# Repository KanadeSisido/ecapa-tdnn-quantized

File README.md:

# anam — The Living Anamnesis

高齢の方の日常の声を 24 時間記録するペンダントと、その記録から「次の診察で先生に伝えること」を整えるアプリ。医療・介護の現場で、ご本人が診察室で思い出せない・言いそびれる生活の様子（アナムネ＝問診・生活歴）を、医師やケアの担い手に届ける。

DevFest GDGoC Japan Hackathon 2026 の提出物。

```text
ペンダント（録音・保存）──BLE、約2時間ごと──▶ スマホアプリ（anam）──HTTPS──▶ pendant-api（Cloud Run）──▶ Gemini（Vertex AI）
  赤/黒の表示で録音中を示す            要約・相談・報告書・設定              記録・メモ・設定を保存       要約・診療サマリー・声の聞き取り
```

## できること

| 画面 | 内容 |
|---|---|
| ホーム | ペンダントの録音状態（本体の赤/黒の表示と同じ見た目）、同期・電源・保存量、今日のハイライト |
| 要約 | 本日の要約と、**声で相談**。大きな「押して話す」ボタンで話すと、音声をそのまま Gemini に渡して聞き取り・返答し、返答を読み上げる。相談で出た「診察で伝えるメモ」がたまる |
| 要約 → 医師向け報告書 | チャットではなく、メモ・記録の所見・本日の様子を 1 枚にまとめ、OS の共有シートで医師に渡す |
| ログ | 日ごとの文字起こし・要約・録音データの情報 |
| 診療 | 次回診療向けの「気になる点」。記録から Gemini で作り直せる |
| 設定 | 「クラウドに送信する」（初期値オフ）、「返答を読み上げる」、開発者向けの BLE 同期画面 |

起動時に、ロゴ（ペンダントに A を刻んだ形）が描かれる約 2 秒のアニメーションが出る。

## Google の技術

- **Gemini（Vertex AI 経由）**: 1 日の要約、診療向けサマリー（気になる点）、要約タブの相談、**声の相談（音声を直接渡して、聞き取りと返答を 1 回で得る）**。
- **Cloud Run**: pendant-api（FastAPI）をデプロイ。

## プライバシーの考え方

- **クラウド送信は初期値オフ。** オンにするときは確認ダイアログで同意を取る。オフの間、サーバーは Gemini に何も送らない（声の相談は 409 で断る）。
- 録音した相談の声は、送信後に端末から消す。
- ペンダントは録音中に前面が赤く、電源が切れると黒になる。周りの人にも録音していることが分かる。
- 診断はしない。画面と報告書に「自動要約であり診断ではない」と明記する。

## リポジトリの構成

| パス | 内容 |
|---|---|
| `pendant/mobile/` | アプリ（Android: Kotlin / Compose、iOS: SwiftUI、共通の同期ロジック: Kotlin Multiplatform）。[README](pendant/mobile/README.md)、画面の自動録画は [demo/](pendant/mobile/demo/README.md) |
| `pendant/fw/` | ペンダントのファームウェア（nRF54L15、Zephyr / NCS） |
| `pendant/hw/` | ペンダントの基板（KiCad）。Standard（CR2477）と Premium（Solar＋蓄電） |
| `pendant/docs/spec/` | ペンダントの仕様（電源・音声・保存・同期形式・RF・筐体など） |
| `pendant/brand/` | ロゴ（SVG）とアプリアイコン |
| `export/`、`app/`、`report/` | 話者照合（ECAPA-TDNN を INT8 化してスマホで動かす）の PoC。[下記](#話者照合-pocecapa-tdnn) |
| `server/` | pendant-api。API 仕様は `server/API.md`、デプロイは `server/deploy.sh` |

## アプリを動かす

1. サーバーの URL とトークンを置く（**Git に入れない**。トークンはチームから受け取る）。
   - Android: `pendant/mobile/local.properties` に `pendant.api.base=https://…` と `pendant.api.token=…`
   - iOS: `pendant/mobile/iosApp/Sources/Secrets.plist` に `ApiBase` と `ApiToken`（文字列）
   - 置かなければ、固定のデモデータと台本の返答で動く（サーバー無しで画面を見られる）。
2. ビルドする。
   ```bash
   cd pendant/mobile && source env.sh && ./gradlew :androidApp:assembleDebug   # APK: androidApp/build/outputs/apk/debug/
   ```
   iOS は `pendant/mobile/iosApp/iosApp.xcodeproj` を Xcode で開いて実行する（Kotlin の共通部分はビルド時に自動で作られる）。
3. 声の相談を使うときは、設定タブで「クラウドに送信する」をオンにする。

## デモの流れ（例）

1. 起動アニメーション → ホームで「録音中」（ペンダントの赤い表示と同じ）を見せる。
2. 要約タブで「押して話す」→「最近、膝が痛くて夜も眠れないの。先生に伝えておいてほしい」と話す → 返答が読み上げられ、メモに残る。
3. 「医師向け報告書にまとめる」→ 共有シートで送る。
4. 診療タブで「記録から作り直す（Gemini）」。
5. 終わったら、サーバーに残った会話とメモを消しておく（相談の文脈に混ざるため）。
   ```bash
   curl -X DELETE -H "Authorization: Bearer $TOKEN" $URL/assistant/messages
   ```

## 既知の制約

- サーバーの DB はデモ用（Cloud Run の `/tmp` に置いた SQLite）。再デプロイ・再起動で初期データに戻り、「クラウドに送信する」もオフに戻る。
- ペンダント本体（Premium）は試作段階で、電源・録音時間の実測は済んでいない。デモのアプリはサーバーのデモデータを表示する。
- 話者照合（ECAPA）は PoC で、モバイルアプリにはまだ組み込んでいない。
- Android の声の相談は、実機での録音から返答までの通しを確認していない（iOS Simulator では確認済み）。

---

## 話者照合 PoC（ECAPA-TDNN）

SpeechBrain `spkrec-ecapa-voxceleb` を ONNX + INT8 に変換し、Flutter（ONNX Runtime）で
「登録音声と今の発話が同一人物か」をオンデバイスで判定する。

### 構成

```
export/                 Python: 変換・量子化・評価
  export_onnx.py        生波形→埋め込み を1本の ONNX に（Fbank もグラフに同梱）
  prepare_data.py       評価用 LibriSpeech test-clean 抽出（40話者×12発話）
  quantize_eval.py      INT8 量子化（dynamic / static QDQ）＋ EER・速度比較 → app/assets にコピー
  check_ort115.py       Flutter 同梱の ORT 1.15.1 でロードできるか確認
app/                    Flutter アプリ（Android / iOS）
  lib/speaker_verifier.dart  ORT 推論・コサイン類似度・PCM変換・簡易VAD
  lib/main.dart              登録（3回）→ 照合 UI、閾値スライダー
```

### 再生成手順

```bash
cd export
uv sync                       # torch 等で約1.3GB
uv run python export_onnx.py  # models/ecapa_fp32.onnx
uv run python prepare_data.py
uv run python quantize_eval.py
## 任意: 古い ORT での互換確認（新しい glibc では GLIBC_TUNABLES が必要）
GLIBC_TUNABLES=glibc.rtld.execstack=2 uv run --no-project --python 3.11 \
  --with onnxruntime==1.15.1 --with "numpy<2" --with soundfile python check_ort115.py

cd ../app
flutter run   # 実機推奨（マイクを使うため）
```

### 結果（LibriSpeech test-clean、キャリブ話者を除く 31話者433発話 / 先頭4秒、x86 CPU 1スレッド）

| model | size | EER | EER閾値 | fp32との cos | 3秒音声の推論 |
|---|---|---|---|---|---|
| fp32 | 84.1 MB | 0.80 % | 0.327 | 1.000 | 226 ms |
| int8 dynamic | 22.0 MB | 0.78 % | 0.334 | 0.995 | 320 ms |
| **int8 static (QDQ)** ← 採用 | 25.8 MB | 0.78 % | 0.329 | 0.996 | **46 ms** |

※ 評価セットは小さく、条件の良い英語の読み上げ音声。実運用では日本語・実機マイク・雑音環境での再評価と閾値調整が必須。

### ハマりどころ（対処済み）

- **ASP のマスク長計算まで量子化すると可変長入力で壊れる** → 量子化対象を Conv/MatMul に限定
- **ORT 1.31 の QDQ 融合が最終 fc Conv でクラッシュ** → そのノードだけ FP32 のまま
- **量子化ツールが付ける未使用 opset（ai.onnx.ml v5 等）で ORT 1.15 がロード拒否** → 未使用の opset 宣言を削除
- 前処理（DFT conv / log-mel）は FP32 のまま（量子化すると精度が落ちるため）

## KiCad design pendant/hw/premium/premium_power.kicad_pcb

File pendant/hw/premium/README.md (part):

# Premium power: circuit draft for review only

**Do not connect a real primary cell or hybrid capacitor (including Vina VPC and Eaton HSH/HSL).** Bare-board [prototype fabrication files](fab/README.md) are available for evaluation, but this electrical draft is not qualified for real-cell operation. D1 = BAT41ZFILM and R6 = 1.2 kΩ 1% are **emulator-only screening candidates**, not qualified primary-cell protection. They are placed before every primary branch including BQ25505 VBAT_PRI, consistent with Panasonic's [primary-cell caution](https://industrial.panasonic.com/cdbs/www-data/pdf/AAA4000/AAA4000COL15.pdf). Check the exact cell's reverse charge and fault requirements, leakage, forward drop, surge and operating temperatures. LM66100 U4 does not replace that requirement. Confirm diode-short, reversed-cell and failure current limits.

The demo evaluation target is a single CR2032 backup cell for 24 hours. SMD components are on the front; provisional through-hole footprints put the CH005-2032LF holder and horizontal Vina capacitor side by side on the back, with their leads hand-soldered from the front. Bare test pads are also on the back and have been moved outside their approximate courtyards. Pad-in-via is accepted for home assembly, subject to solder wicking and insulation checks. The user reported physical checks of the holder and capacitor on 2026-11-06; individual measured values were not supplied. Enclosure interference, test-pad access and backup runtime remain unverified. The selected first evaluation panel is the uxcell round 36 mm candidate, whose actual Voc, MPP and thickness have not been measured. R3/R4/R5 now use 787 kΩ / 6.34 MΩ / 4.87 MΩ, 0.1%, for nominal falling/rising VBAT_OK of 2.785 / 2.981 V. This gives the Vina 30 F's 2.5 V operating floor more static margin than the prior draft; it does not protect against self-discharge in storage or establish dynamic margin. It also reduces available energy before switching. See the design calculation and bench conditions. The new divider remains an evaluation candidate, not evidence that the schematic is safe or complete.

The candidate source paths are `VSTOR → U3 LM66100 → Q1 common-source back-to-back → VOR`, and `cell emulator → D1 → R6 → COIN → U4 LM66100 → Q2 common-source back-to-back → VOR`. BQ VBAT_PRI is sensed at COIN, downstream of D1/R6. Both LM66100 comparators use CE=their own VOUT. A LM66100 permits transient and small reverse current and has temperature-dependent leakage. Neither the primary cell nor the secondary energy path has been proven safe, and all startup and switching states require bench measurement with emulators.

For C1/C3/C5/C6, 10 µF 16 V and 0805 are provisional, with [Yageo CC0805KRX5R7BB106](https://www.yageogroup.com/download/specsheet/CC0805KRX5R7BB106) as a candidate. Actual capacitors still need bias, tolerance, temperature and leakage checks; the BQ solar input and VSTOR each require ≥4.7 µF **effective**. C8 is an intentionally unselected primary-side reservoir after D1/R6; its 1210 footprint is a placement placeholder, not a capacitance selection. Its value, actual size, leakage and failure effects are not validated, and VOR holdup is also not sized. J1 has provisional solder-wire pads; J2 and J3 use evaluation footprints for the horizontal Vina capacitor and CH005-2032LF holder. On 2026-11-06 the user reported checking both physical parts, including terminal polarity, hole locations and lead bends; measured values were not recorded. L1's Coilcraft land pattern has been compared with [LPS4018](https://www.coilcraft.com/getmedia/31b05c96-4c4c-4498-8dbb-fe092de76bad/lps4018.pdf). L2 now uses a local footprint with nominal pad dimensions following the [DFE201612E recommended pattern](https://elektronik.ropla.eu/pdf/stock/mur/dfe201612eseries.pdf); assembly remains untested.

The local `premium.pretty` library contains provisional TI RGR0020A and CSD75208W1015 footprints. BQ's external copper pads and four exposed-pad paste openings follow the example dimensions in the [BQ25505 package drawing](https://www.ti.com/lit/ds/symlink/bq25505.pdf). The CSD top-view copper pattern follows [TI §7.2](https://www.ti.com/lit/gpn/csd75208w1015), but **its F.Paste is intentionally absent**: a stencil generated as-is will have no paste openings for Q1/Q2. Determine the stencil and solder-mask design with the assembler before fabrication. Both footprints still need manufacturing and assembly verification, including BQ thermal vias if used. NAND's 8 × 6 mm / 1.27 mm pitch and nominal 3.4 × 4.3 mm exposed pad match the [F35UQA512M package drawing](https://cdn.icstop.com/upload/pdfs/e7/de/e7decc6bb7e9f2384da286e27083f166.pdf), but its EP electrical treatment and stencil need confirmation.

BQ NC pins 6/16/17 and exposed pad connect to GND. U2 is the provisional TPS62842DGRR, selected from the TPS62840 family because the smaller TPS62840DLCR was unavailable from the checked distributor. Its DGR package is larger and **not pin-compatible** with DLC: VSET pin 4 = GND selects 1.8 V, pin 7 is NC, and exposed pad 9 = GND. The unused DLC STOP function has no DGR pin. The provisional KiCad generic footprint has 0.50 mm outer pad width versus 0.30 mm in TI's land example; EP mask and paste also differ. Confirm the selected footprint and stencil with the assembler, along with output accuracy, effective capacitance and transients before PCB release. [TI device comparison, Table 1 and package example](https://www.ti.com/lit/ds/symlink/tps62840.pdf).

U5 is the SN74LVC1G17DBVR evaluation buffer: DBV pin 1 NC, 2 A from VBAT_OK_RAW, 3 GND, 4 Y to VBAT_OK_1V8, 5 VCC=1V8, with C7 100 nF. Its output goes to U103 B2/P0.03; TP12 is raw VBAT_OK and must not connect to a 1.8 V GPIO. Verify input thresholds, leakage, rail-off back-power, the input state when VSTOR is absent but the primary source powers 1V8, and the energy budget before adoption. [TI pinout and Ioff](https://www.ti.com/lit/ds/symlink/sn74lvc1g17.pdf). No HSL/COIN voltage dividers are connected: a divider alone must not energize a powered-off MCU through its ADC. P1.05/AIN1 is reserved but unconnected.

## Demo shared core and measurements

The sheet includes the BC15M U103, F35UQA512M U105, T5848 U108, microphone switch/buffer, button and SWD pogo from the Standard definitions. The optional external RTC and terminal-indicator circuits are omitted for this demo; no claim is made that the omitted product functions work. SW101 is a **bridged solder jumper**, not an operable privacy latch. Select and validate the actual physical control and check mic SD/WAKE back-power and isolation.

For the demo, NAND shares 1V8 through 0 Ω R106 and is **not independently power-gated**. This avoids the previous steady state in which a powered MCU could drive an unpowered NAND's pins, and removes the load switch and EN pulldown. It does not prove ramp or signal-transition behavior. The NAND datasheet gives 10 µA typ / 50 µA max standby under its stated conditions: account for that separately, rather than reusing a gated-NAND energy estimate. NAND remains powered on the coin source; firmware must separately prevent unqualified writes, erases, BLE and OTA. Before opening R106 for current measurement, de-energize and connect the meter without leaving a powered MCU driving an unpowered NAND; verify the meter's burden and all transitions.

R7 is the 1V8 main measurement link, R8 is the CAP measurement link; TP1–TP12 expose SOLAR, BQ-side HSL, VSTOR, protected COIN, VOR, 1V8_BUCK, SEC_GATE, PRI_GATE, CAP_EXT, MIC_EN, VBAT_OK_1V8 and VBAT_OK_RAW respectively. TP104/105/106/107 expose 1V8, NAND_1V8, MIC_1V8 and GND; the core also retains UART, marker and MIC_1V8_PRE points. J1 is a provisional solar interface; J2 and J3 use provisional physical capacitor and holder footprints whose mechanics and polarity require verification. The test fixture must not bypass the primary protection or become a USB supply path in the demo.

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
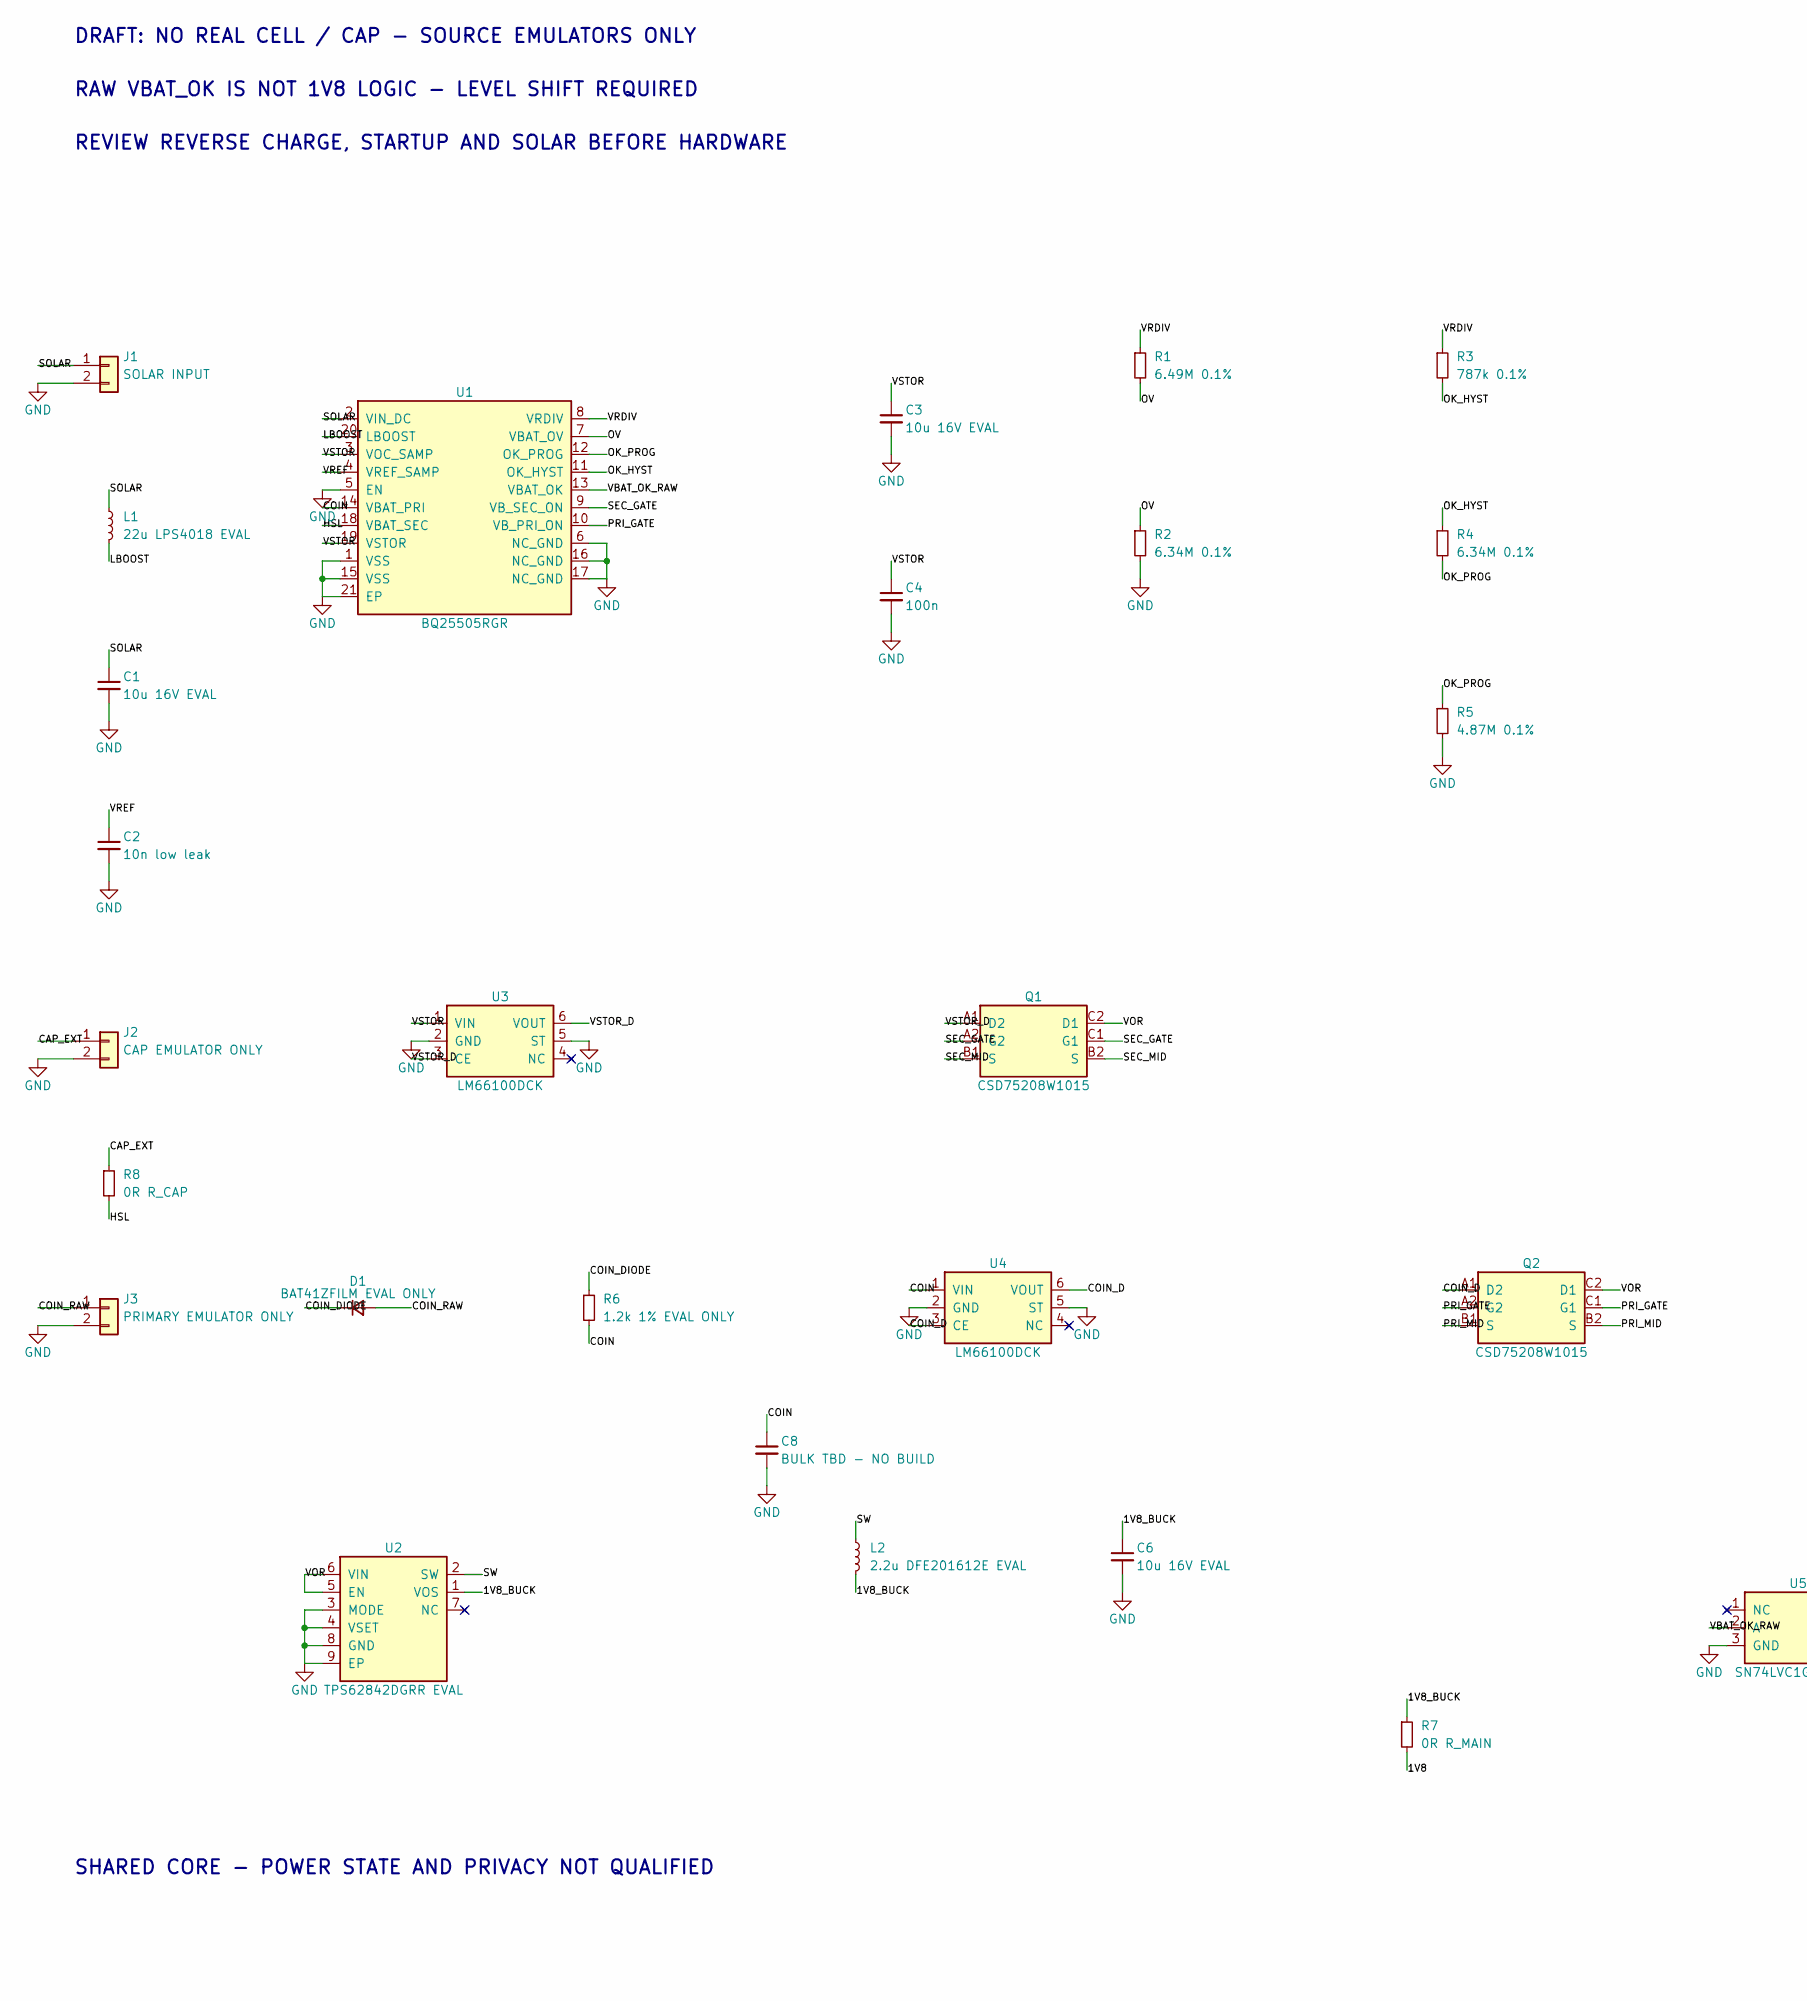
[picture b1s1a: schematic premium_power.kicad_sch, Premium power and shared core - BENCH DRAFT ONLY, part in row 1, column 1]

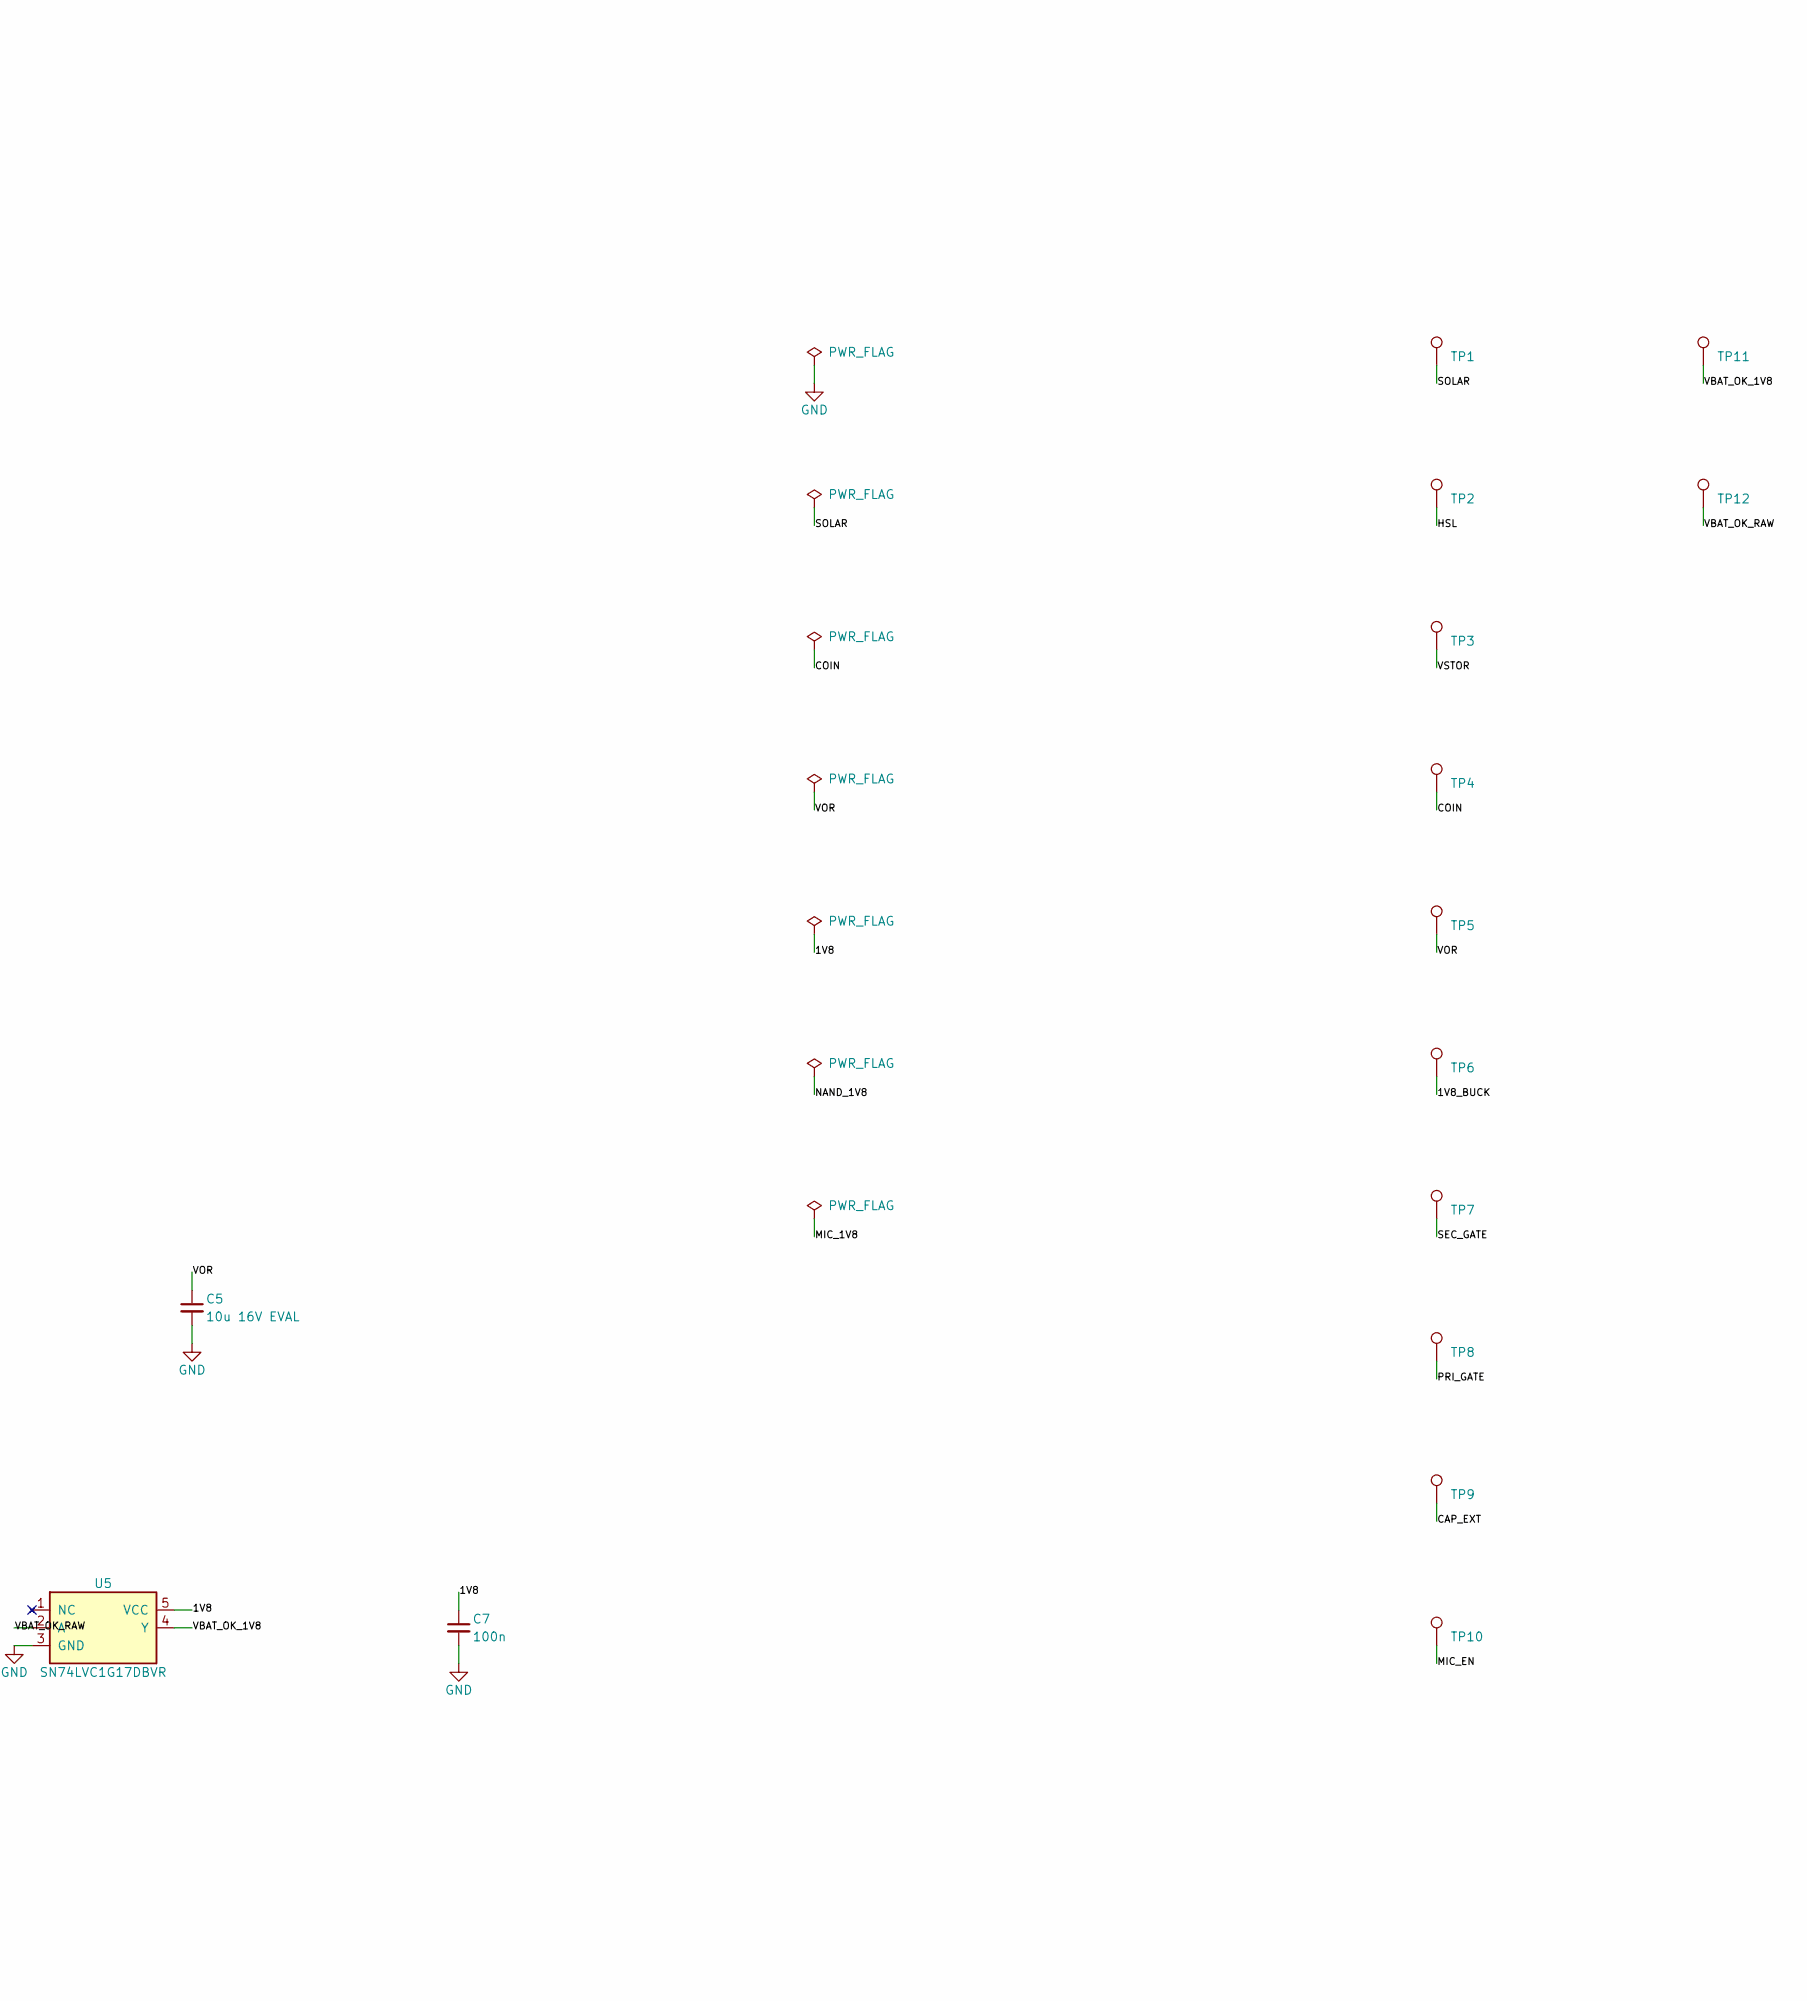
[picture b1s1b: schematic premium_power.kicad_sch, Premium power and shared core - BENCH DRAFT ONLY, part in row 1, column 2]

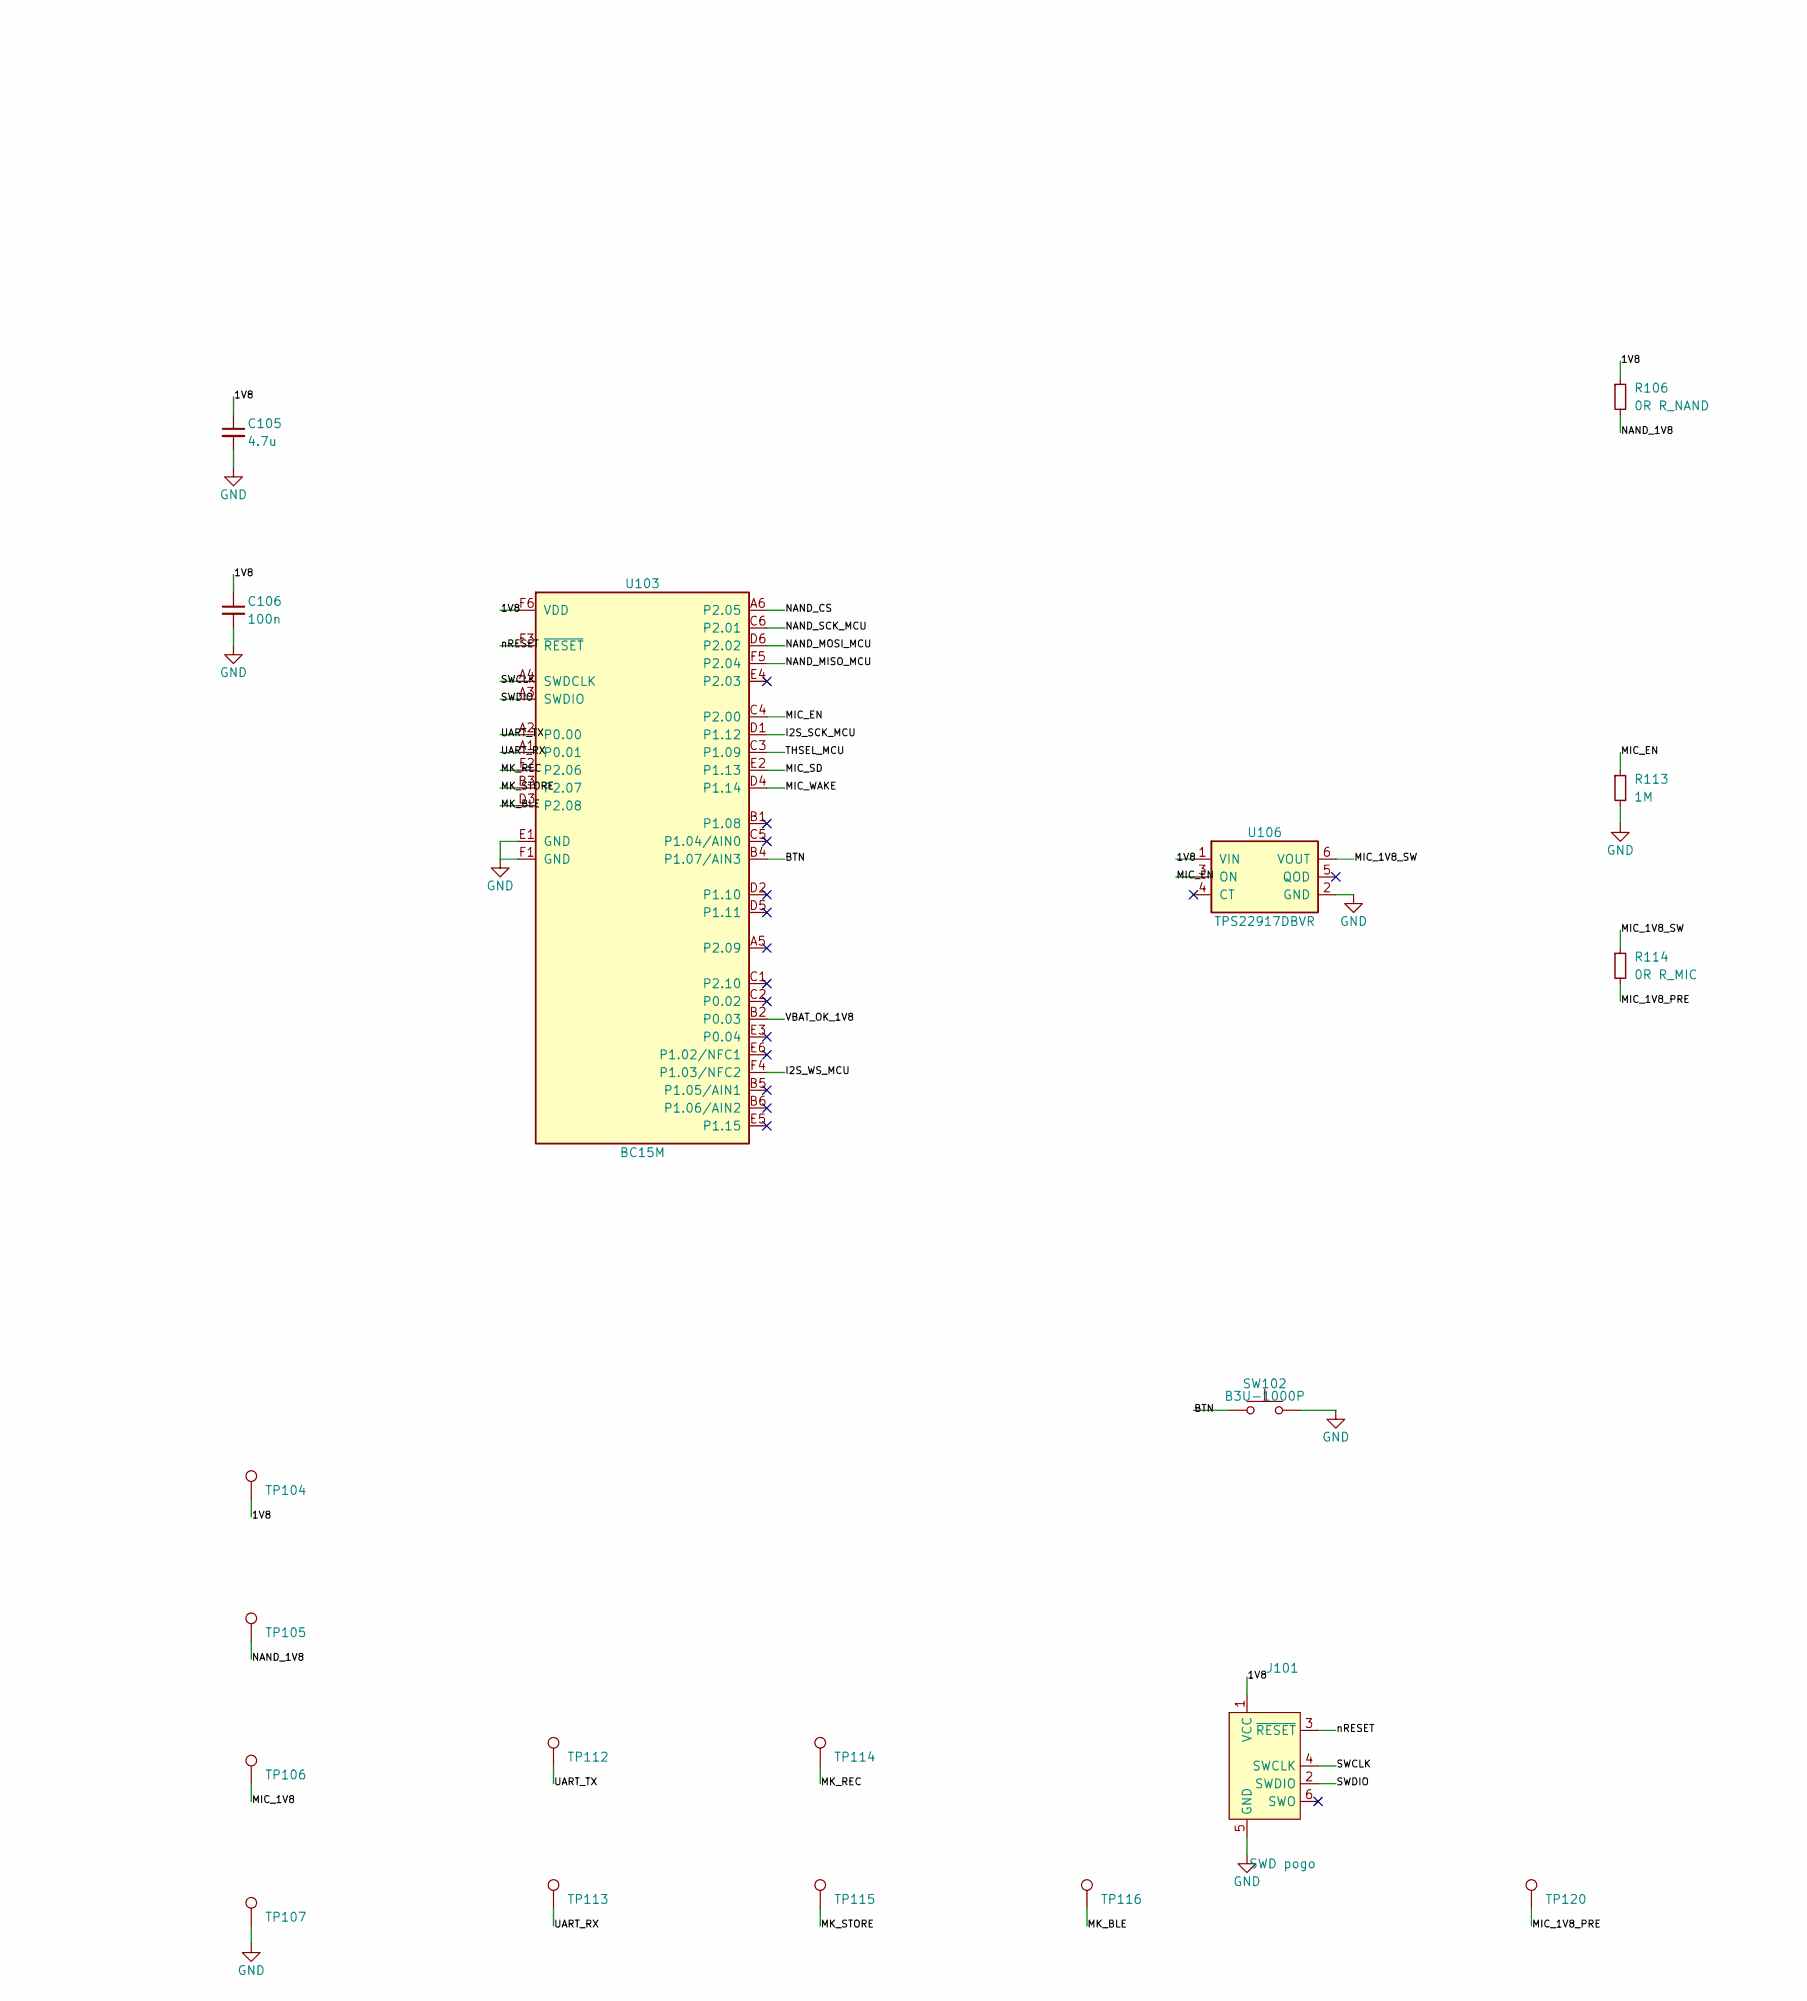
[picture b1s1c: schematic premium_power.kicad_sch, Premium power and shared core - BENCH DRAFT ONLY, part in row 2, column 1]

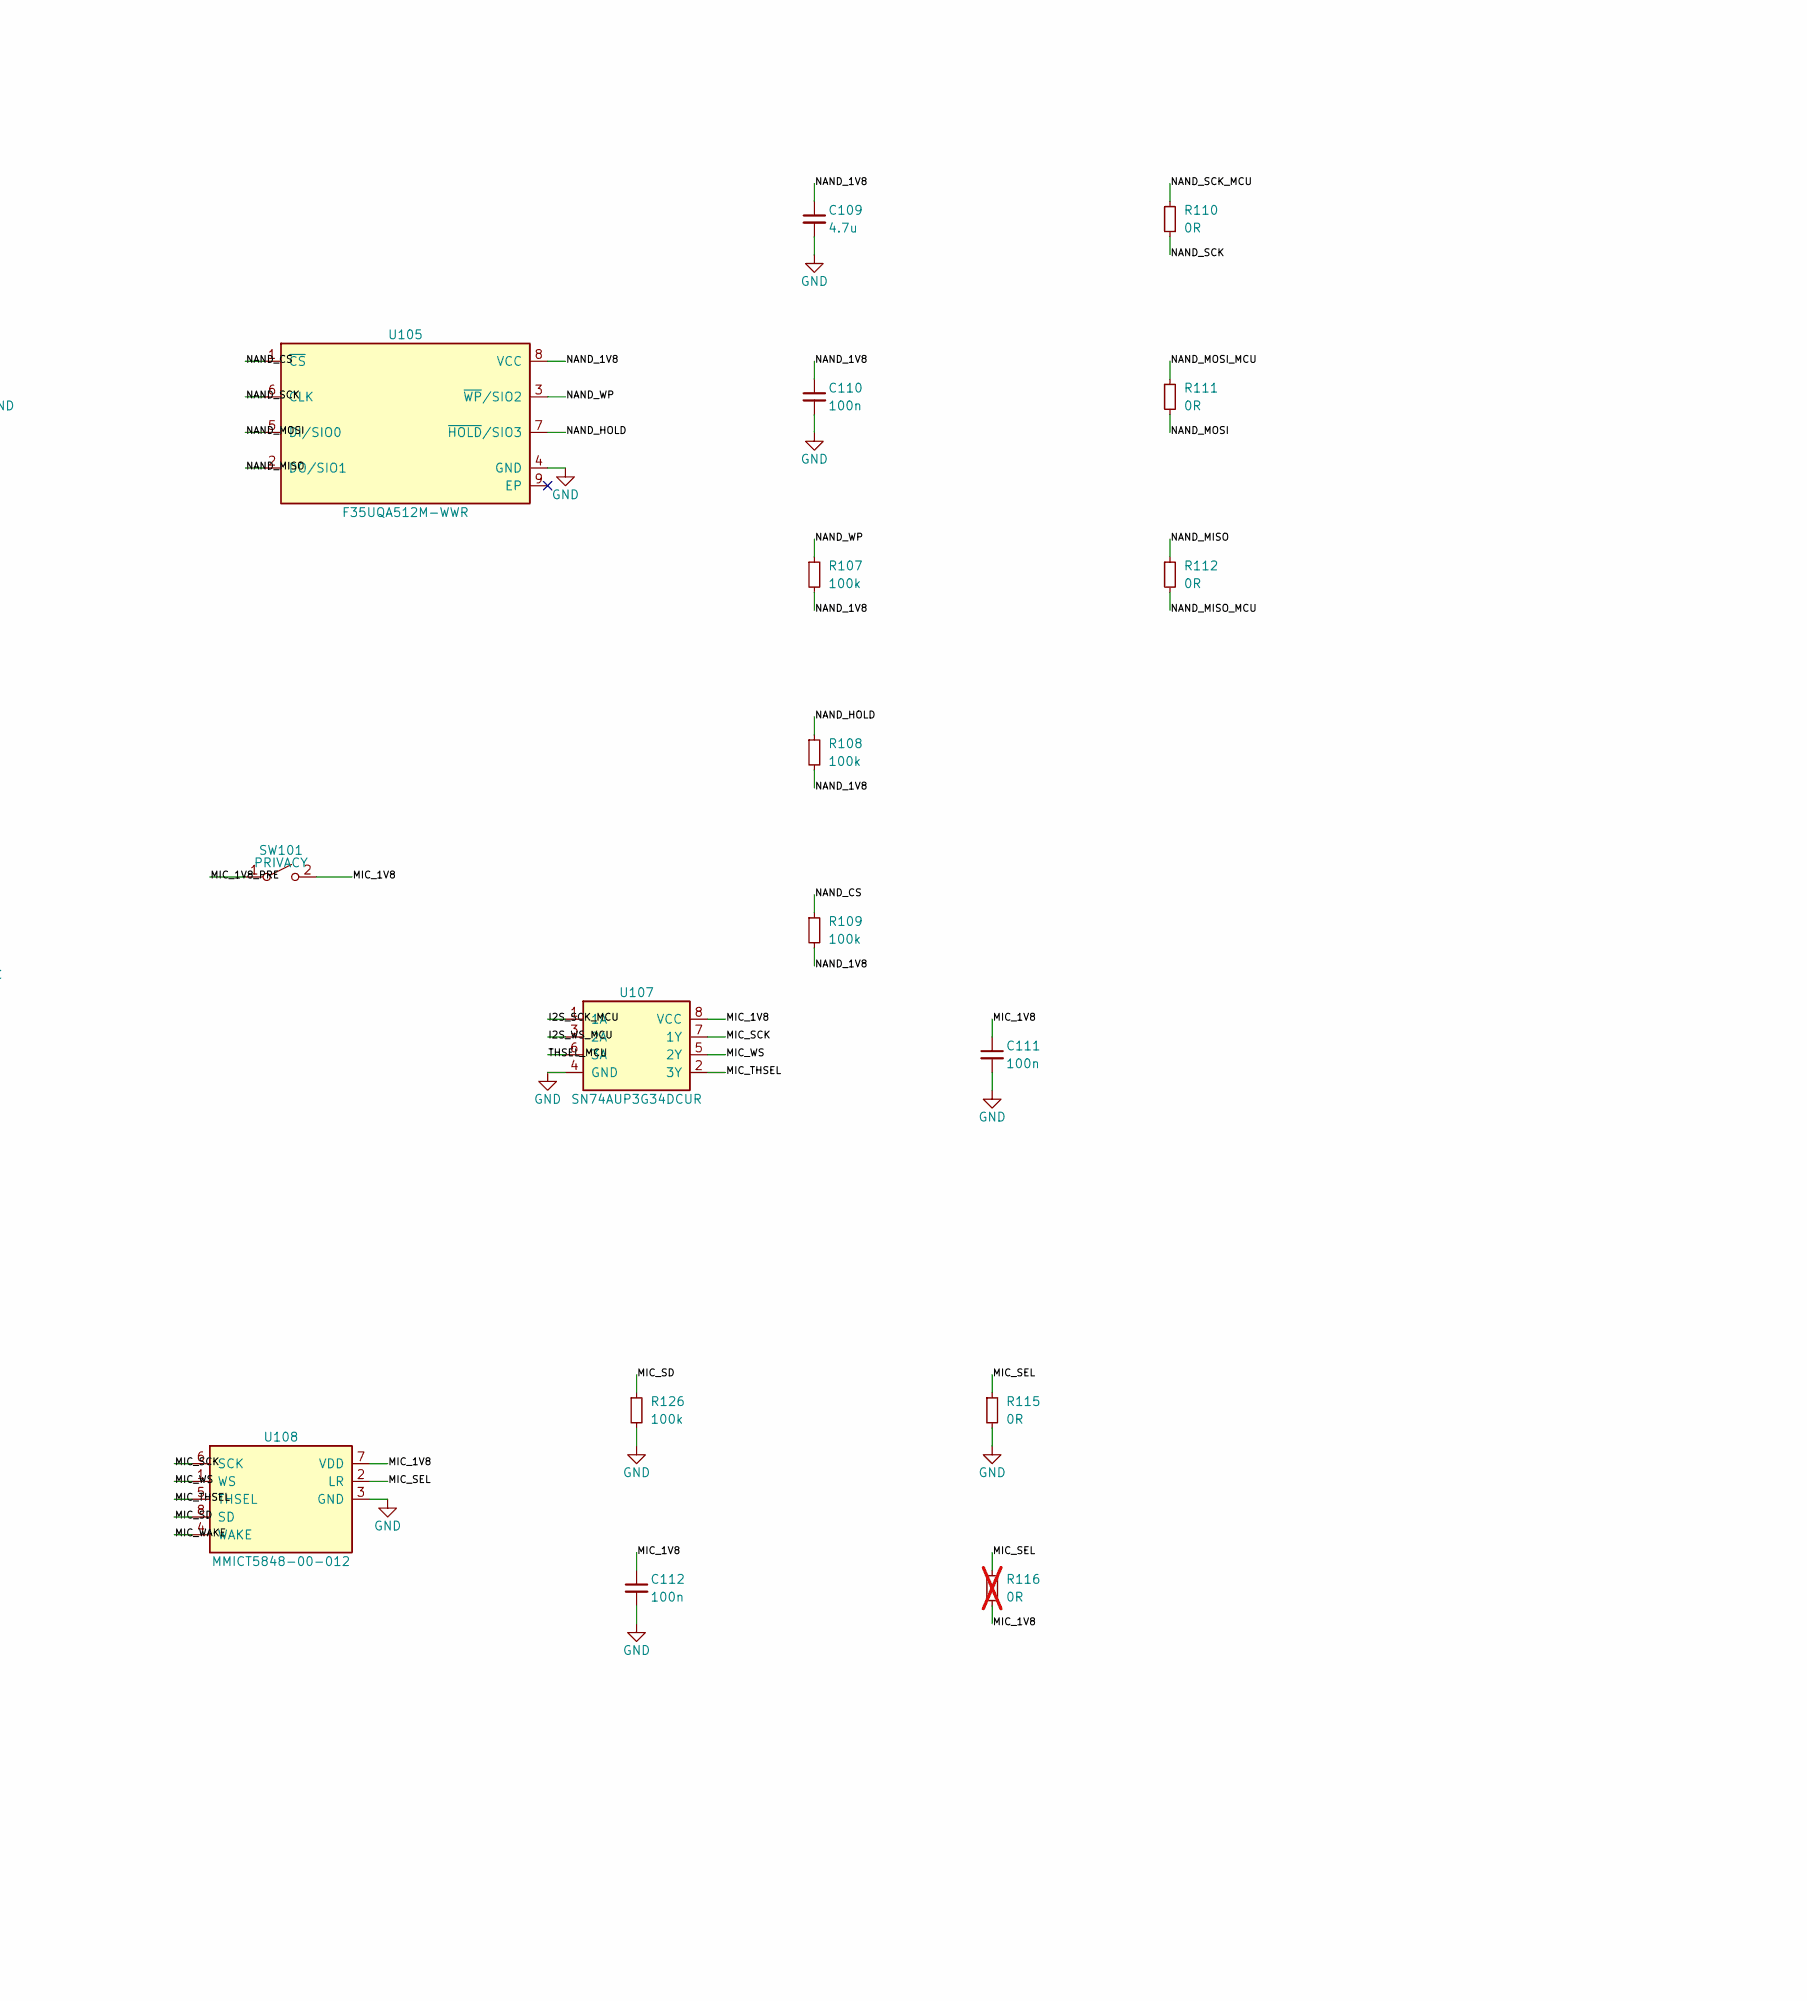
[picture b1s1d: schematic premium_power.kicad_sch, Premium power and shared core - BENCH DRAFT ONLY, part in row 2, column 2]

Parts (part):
C1, C3, C5, C6: 10u 16V EVAL; C_0805_2012Metric
C2: 10n low leak; C_0402_1005Metric
C4, C7, C106, C110, C111, C112: 100n; C_0402_1005Metric
C8: BULK TBD - NO BUILD; C_1210_3225Metric
C105: 4.7u; C_0402_1005Metric; MPN Murata GRM155R61A475MEAAD
C109: 4.7u; C_0402_1005Metric
D1: BAT41ZFILM EVAL ONLY; D_SOD-123
J1: SOLAR INPUT; SolderWire-0.15sqmm_1x02_P4mm_D0.5mm_OD1.5mm
J2: CAP EMULATOR ONLY; Vina_VEL08203R8306G_Bottom_Horizontal_Eval
J3: PRIMARY EMULATOR ONLY; CH005_2032LF_Bottom_Eval_PolarityHypothesis
J101: SWD pogo; SWD_Pogo_2x03_P1.27mm_NoHoles
L1: 22u LPS4018 EVAL; L_Coilcraft_LPS4018
L2: 2.2u DFE201612E EVAL; L_Murata_DFE201612E_Eval
Q1, Q2: CSD75208W1015; TI_CSD75208W1015_Eval
R1: 6.49M 0.1%; R_0402_1005Metric
R2, R4: 6.34M 0.1%; R_0402_1005Metric
R3: 787k 0.1%; R_0402_1005Metric
R5: 4.87M 0.1%; R_0402_1005Metric
R6: 1.2k 1% EVAL ONLY; R_0603_1608Metric
R7: 0R R_MAIN; R_0603_1608Metric
R8: 0R R_CAP; R_0603_1608Metric
R106: 0R R_NAND; R_0402_1005Metric
R107, R108, R109, R126: 100k; R_0402_1005Metric
R110, R111, R112, R115: 0R; R_0402_1005Metric
R113: 1M; R_0402_1005Metric
R114: 0R R_MIC; R_0402_1005Metric
R116: 0R; R_0402_1005Metric; not fitted
SW101: PRIVACY; SolderJumper-2_P1.3mm_Bridged_RoundedPad1.0x1.5mm
SW102: B3U-1000P; SW_SPST_B3U-1000P
TP1: SOLAR; TestPoint_Pad_D1.0mm
TP2: HSL; TestPoint_Pad_D1.0mm
TP3: VSTOR; TestPoint_Pad_D1.0mm
TP4: COIN; TestPoint_Pad_D1.0mm
TP5: VOR; TestPoint_Pad_D1.0mm
TP6: 1V8_BUCK; TestPoint_Pad_D1.0mm
TP7: SEC_GATE; TestPoint_Pad_D1.0mm
TP8: PRI_GATE; TestPoint_Pad_D1.0mm
TP9: CAP_EXT; TestPoint_Pad_D1.0mm
TP10: MIC_EN; TestPoint_Pad_D1.0mm
TP11: VBAT_OK_1V8; TestPoint_Pad_D1.0mm
TP12: VBAT_OK_RAW; TestPoint_Pad_D1.0mm
TP104: 1V8; TestPoint_Pad_D1.0mm
TP105: NAND_1V8; TestPoint_Pad_D1.0mm
TP106: MIC_1V8; TestPoint_Pad_D1.0mm
TP107: GND; TestPoint_Pad_D1.0mm
TP112: UART_TX; TestPoint_Pad_D1.0mm
TP113: UART_RX; TestPoint_Pad_D1.0mm
TP114: MK_REC; TestPoint_Pad_D1.0mm
TP115: MK_STORE; TestPoint_Pad_D1.0mm
TP116: MK_BLE; TestPoint_Pad_D1.0mm
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
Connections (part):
/1V8: C7.1, C105.1, C106.1, J101.1 (VCC), R7.2, R106.1, TP104.1, U5.5 (VCC), U103.F6 (VDD), U106.1 (VIN)
/1V8_BUCK: C6.1, L2.2, R7.1, TP6.1, U2.1 (VOS)
/BTN: SW102.1, U103.B4 (P1.07/AIN3)
/CAP_EXT: J2.1, R8.1, TP9.1
/COIN: C8.1, R6.2, TP4.1, U1.14 (VBAT_PRI), U4.1 (VIN)
/COIN_D: Q2.A1 (D2), U4.3 (CE), U4.6 (VOUT)
/COIN_DIODE: D1.1 (K), R6.1
/COIN_RAW: D1.2 (A), J3.1
/HSL: R8.2, TP2.1, U1.18 (VBAT_SEC)
/I2S_SCK_MCU: U103.D1 (P1.12), U107.1 (1A)
/I2S_WS_MCU: U103.F4 (P1.03/NFC2), U107.3 (2A)
/LBOOST: L1.2, U1.20 (LBOOST)
/MIC_1V8: C111.1, C112.1, R116.2, SW101.2 (B), TP106.1, U107.8 (VCC), U108.7 (VDD)
/MIC_1V8_PRE: R114.2, SW101.1 (A), TP120.1
/MIC_1V8_SW: R114.1, U106.6 (VOUT)
/MIC_EN: R113.1, TP10.1, U103.C4 (P2.00), U106.3 (ON)
/MIC_SCK: U107.7 (1Y), U108.6 (SCK)
/MIC_SD: R126.1, U103.E2 (P1.13), U108.8 (SD)
/MIC_SEL: R115.1, R116.1, U108.2 (LR)
/MIC_THSEL: U107.2 (3Y), U108.5 (THSEL)
/MIC_WAKE: U103.D4 (P1.14), U108.4 (WAKE)
/MIC_WS: U107.5 (2Y), U108.1 (WS)
/MK_BLE: TP116.1, U103.D3 (P2.08)
/MK_REC: TP114.1, U103.F2 (P2.06)
/MK_STORE: TP115.1, U103.B3 (P2.07)
/NAND_1V8: C109.1, C110.1, R106.2, R107.2, R108.2, R109.2, TP105.1, U105.8 (VCC)
/NAND_CS: R109.1, U103.A6 (P2.05), U105.1 (~CS)
/NAND_HOLD: R108.1, U105.7 (~HOLD/SIO3)
/NAND_MISO: R112.1, U105.2 (DO/SIO1)
/NAND_MISO_MCU: R112.2, U103.F5 (P2.04)
/NAND_MOSI: R111.2, U105.5 (DI/SIO0)
/NAND_MOSI_MCU: R111.1, U103.D6 (P2.02)
/NAND_SCK: R110.2, U105.6 (CLK)
/NAND_SCK_MCU: R110.1, U103.C6 (P2.01)
/NAND_WP: R107.1, U105.3 (~WP/SIO2)
/OK_HYST: R3.2, R4.1, U1.11 (OK_HYST)
/OK_PROG: R4.2, R5.1, U1.12 (OK_PROG)
/OV: R1.2, R2.1, U1.7 (VBAT_OV)
/PRI_GATE: Q2.A2 (G2), Q2.C1 (G1), TP8.1, U1.10 (VB_PRI_ON)
/PRI_MID: Q2.B1 (S), Q2.B2 (S)
/SEC_GATE: Q1.A2 (G2), Q1.C1 (G1), TP7.1, U1.9 (VB_SEC_ON)
/SEC_MID: Q1.B1 (S), Q1.B2 (S)
/SOLAR: C1.1, J1.1, L1.1, TP1.1, U1.2 (VIN_DC)
/SW: L2.1, U2.2 (SW)
/SWCLK: J101.4 (SWCLK), U103.A4 (SWDCLK)
/SWDIO: J101.2 (SWDIO), U103.A3 (SWDIO)
/THSEL_MCU: U103.C3 (P1.09), U107.6 (3A)
/UART_RX: TP113.1, U103.A1 (P0.01)
/UART_TX: TP112.1, U103.A2 (P0.00)
/VBAT_OK_1V8: TP11.1, U5.4 (Y), U103.B2 (P0.03)
/VBAT_OK_RAW: TP12.1, U1.13 (VBAT_OK), U5.2 (A)
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
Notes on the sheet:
DRAFT: NO REAL CELL / CAP - SOURCE EMULATORS ONLY
RAW VBAT_OK IS NOT 1V8 LOGIC - LEVEL SHIFT REQUIRED
REVIEW REVERSE CHARGE, STARTUP AND SOLAR BEFORE HARDWARE
SHARED CORE - POWER STATE AND PRIVACY NOT QUALIFIED

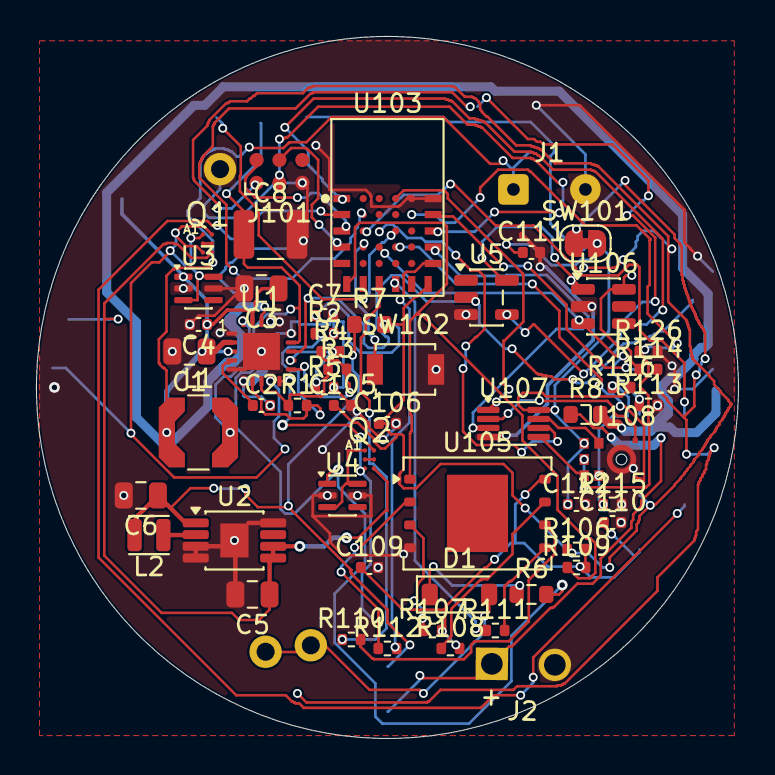
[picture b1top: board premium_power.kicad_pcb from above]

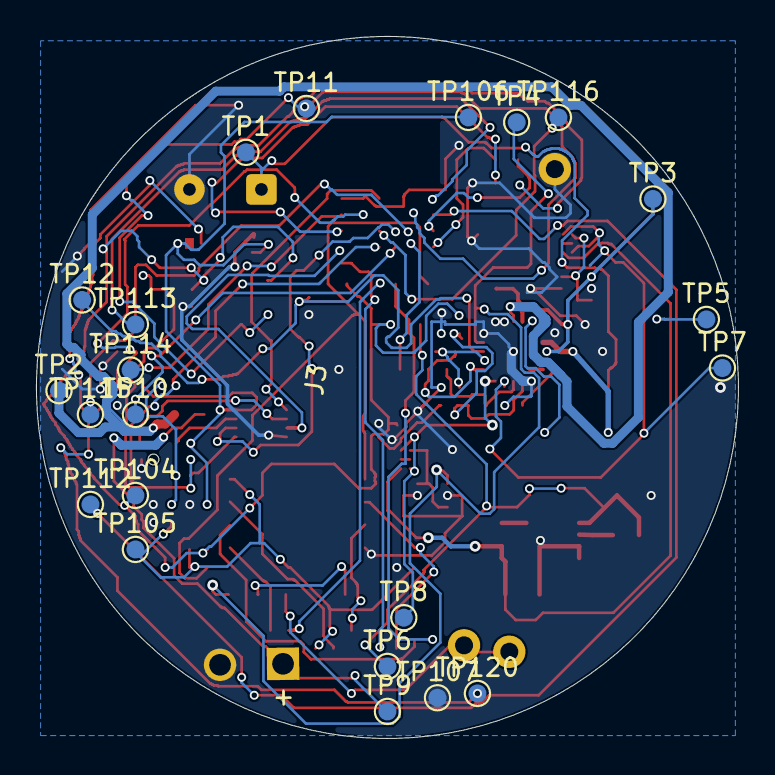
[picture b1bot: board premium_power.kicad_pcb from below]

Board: 2 copper layers, 39.0 x 39.0 mm, 77 parts (23 on the bottom side), 58 nets.
